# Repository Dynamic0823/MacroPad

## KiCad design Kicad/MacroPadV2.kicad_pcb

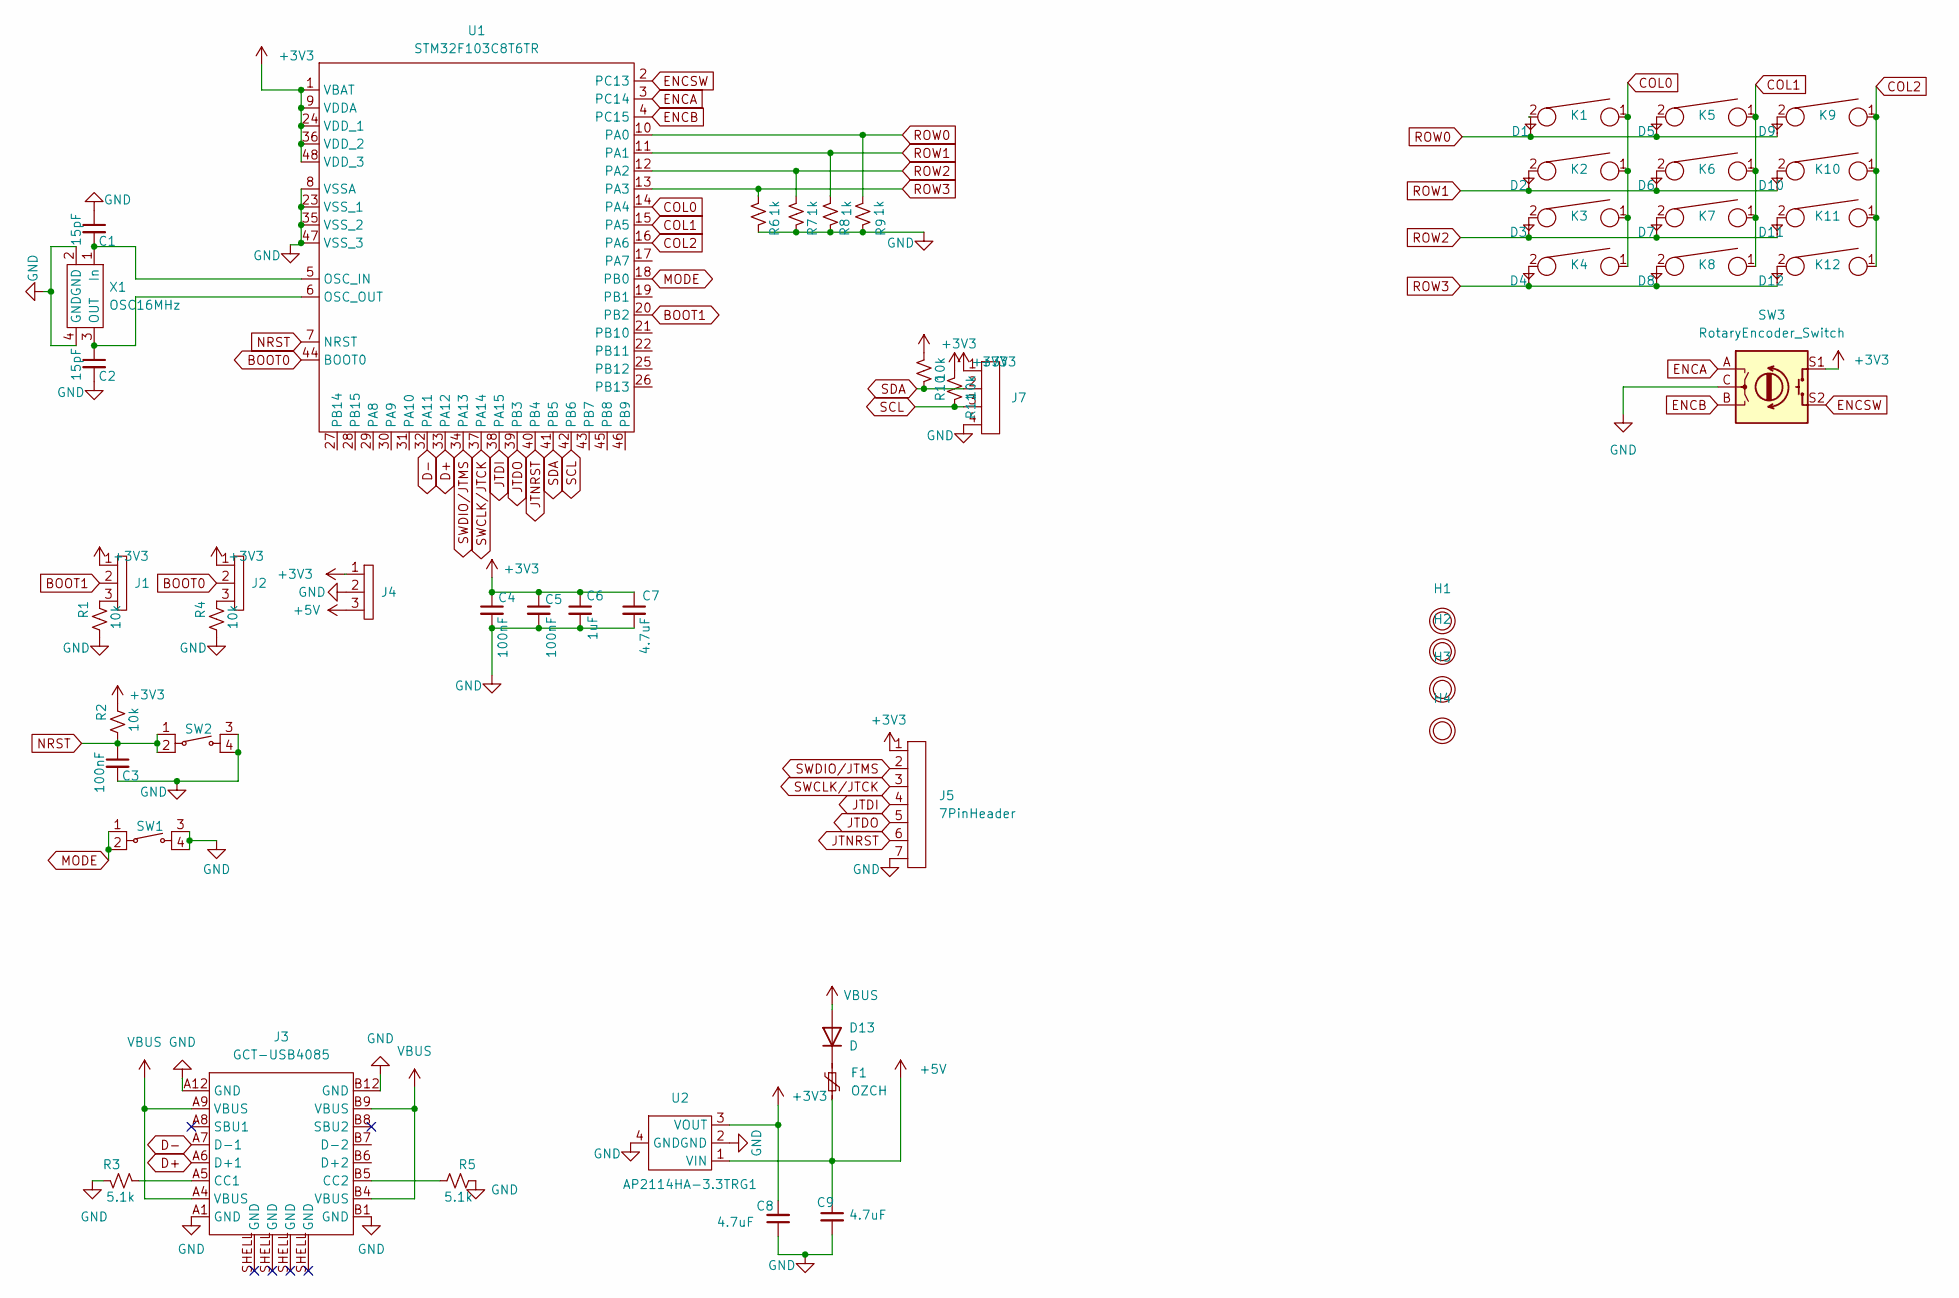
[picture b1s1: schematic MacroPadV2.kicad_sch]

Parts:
C1, C2: 15pF; C_0805_2012Metric_Pad1.18x1.45mm_HandSolder; DigikeyPN 311-1101-2-ND
C3, C4, C5: 100nF; C_0805_2012Metric_Pad1.18x1.45mm_HandSolder; DigikeyPN 3372-MT05B104M500BDTR-ND
C6: 1uF; C_0805_2012Metric_Pad1.18x1.45mm_HandSolder; DigikeyPN 1276-1003-2-ND
C7, C8, C9: 4.7uF; C_0805_2012Metric_Pad1.18x1.45mm_HandSolder; DigikeyPN 1276-1244-2-ND
D1, D2, D3, D4, D5, D6, D7, D8, D9, D10, D11, D12: TS4148 RBG; D_0805_2012Metric_Pad1.15x1.40mm_HandSolder; DigikeyPN 1801-TS4148RBGTR-ND
D13: D; D_0805_2012Metric_Pad1.15x1.40mm_HandSolder; DigikeyPN 1801-TS4148RBGTR-ND
F1: OZCH; OZCHFusr; DigikeyPN 507-1792-2-ND
H1, H2, H3, H4: M3Hole
J1, J2, J4: 3PinJump; PinHeader_1x03_P2.54mm_Vertical
J3: GCT-USB4085; USB4085-GF-A; DigikeyPN 2073-USB4085-GF-ATR-ND
J5: 7PinHeader; PinHeader_1x07_P2.54mm_Vertical
J7: 4PinJump; PinHeader_1x04_P2.54mm_Vertical
K1, K2, K3, K4, K5, K6, K7, K8, K9, K10, K11, K12: KSW; CherryMx; DigikeyPN CH197-ND
R1, R2, R4, R10, R11: 10k; R_0805_2012Metric_Pad1.20x1.40mm_HandSolder; DigikeyPN RMCF0805JT10K0TR-ND
R3, R5: 5.1k; R_0805_2012Metric_Pad1.20x1.40mm_HandSolder; DigikeyPN RMCF0805JT5K10TR-ND
R6, R7, R8, R9: 1k; R_0805_2012Metric_Pad1.20x1.40mm_HandSolder; DigikeyPN RMCF0805FT1K00
SW1, SW2: SWITCH_TACTILE_SPST-NO_0.05A_12V; PTS645-G; DigikeyPN CKN9085TR-ND
SW3: RotaryEncoder_Switch; PEC11H-RotaryEncoderSwitch; DigikeyPN 118-PEC11H-4220F-S0024-ND
U1: STM32F103C8T6TR; LQFP48; DigikeyPN 497-17666-2-ND
U2: AP2114HA-3.3TRG1; SOT-223_DIO-L; DigikeyPN AP2114HA-3.3TRG1DITR-ND
X1: TSX-3225_16.0000MF18X-AC6; TSX-3226; DigikeyPN SER4372TR-ND

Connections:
+3V3: C4.1, C5.1, C6.1, C7.1, C8.2, J1.1, J2.1, J4.1, J5.1, J7.1, R2.1, R10.2, R11.2, SW3.S1, U1.1 (VBAT), U1.9 (VDDA), U1.24 (VDD_1), U1.36 (VDD_2), U1.48 (VDD_3), U2.3 (VOUT)
+5V: C9.1, F1.2, J4.3, U2.1 (VIN)
BOOT0: J2.2, U1.44 (BOOT0)
BOOT1: J1.2, U1.20 (PB2)
COL0: K1.1, K2.1, K3.1, K4.1, U1.14 (PA4)
COL1: K5.1, K6.1, K7.1, K8.1, U1.15 (PA5)
COL2: K9.1, K10.1, K11.1, K12.1, U1.16 (PA6)
D+: J3.A6 (D+1), U1.33 (PA12)
D-: J3.A7 (D-1), U1.32 (PA11)
ENCA: SW3.A, U1.3 (PC14)
ENCB: SW3.B, U1.4 (PC15)
ENCSW: SW3.S2, U1.2 (PC13)
GND: C1.1, C2.2, C3.2, C4.2, C5.2, C6.2, C7.2, C8.1, C9.2, J3.A1 (GND), J3.A12 (GND), J3.B1 (GND), J3.B12 (GND), J4.2, J5.7, J7.4, R1.2, R3.1, R4.2, R5.1, R6.1, R7.1, R8.1, R9.1, SW1.3, SW1.4, SW2.3, SW2.4, SW3.C, U1.8 (VSSA), U1.23 (VSS_1), U1.35 (VSS_2), U1.47 (VSS_3), U2.2 (GND), U2.4 (GND), X1.2 (GND), X1.4 (GND)
JTDI: J5.4, U1.38 (PA15)
JTDO: J5.5, U1.39 (PB3)
JTNRST: J5.6, U1.40 (PB4)
MODE: SW1.1, SW1.2, U1.18 (PB0)
NRST: C3.1, R2.2, SW2.1, SW2.2, U1.7 (NRST)
unnamed: C1.2, U1.5 (OSC_IN), X1.1 (In)
unnamed: C2.1, U1.6 (OSC_OUT), X1.3 (OUT)
unnamed: D1.1, K1.2
unnamed: D2.1, K2.2
unnamed: D3.1, K3.2
unnamed: D4.1, K4.2
unnamed: D5.1, K5.2
unnamed: D6.1, K6.2
unnamed: D7.1, K7.2
unnamed: D8.1, K8.2
unnamed: D9.1, K9.2
unnamed: D10.1, K10.2
unnamed: D11.1, K11.2
unnamed: D12.1, K12.2
unnamed: D13.1 (K), F1.1
unnamed: J1.3, R1.1
unnamed: J2.3, R4.1
unnamed: J3.A5 (CC1), R3.2
unnamed: J3.B5 (CC2), R5.2
ROW0: D1.2, D5.2, D9.2, R9.2, U1.10 (PA0)
ROW1: D2.2, D6.2, D10.2, R8.2, U1.11 (PA1)
ROW2: D3.2, D7.2, D11.2, R7.2, U1.12 (PA2)
ROW3: D4.2, D8.2, D12.2, R6.2, U1.13 (PA3)
SCL: J7.3, R11.1, U1.42 (PB6)
SDA: J7.2, R10.1, U1.41 (PB5)
SWCLK/JTCK: J5.3, U1.37 (PA14)
SWDIO/JTMS: J5.2, U1.34 (PA13)
VBUS: D13.2 (A), J3.A4 (VBUS), J3.A9 (VBUS), J3.B4 (VBUS), J3.B9 (VBUS)

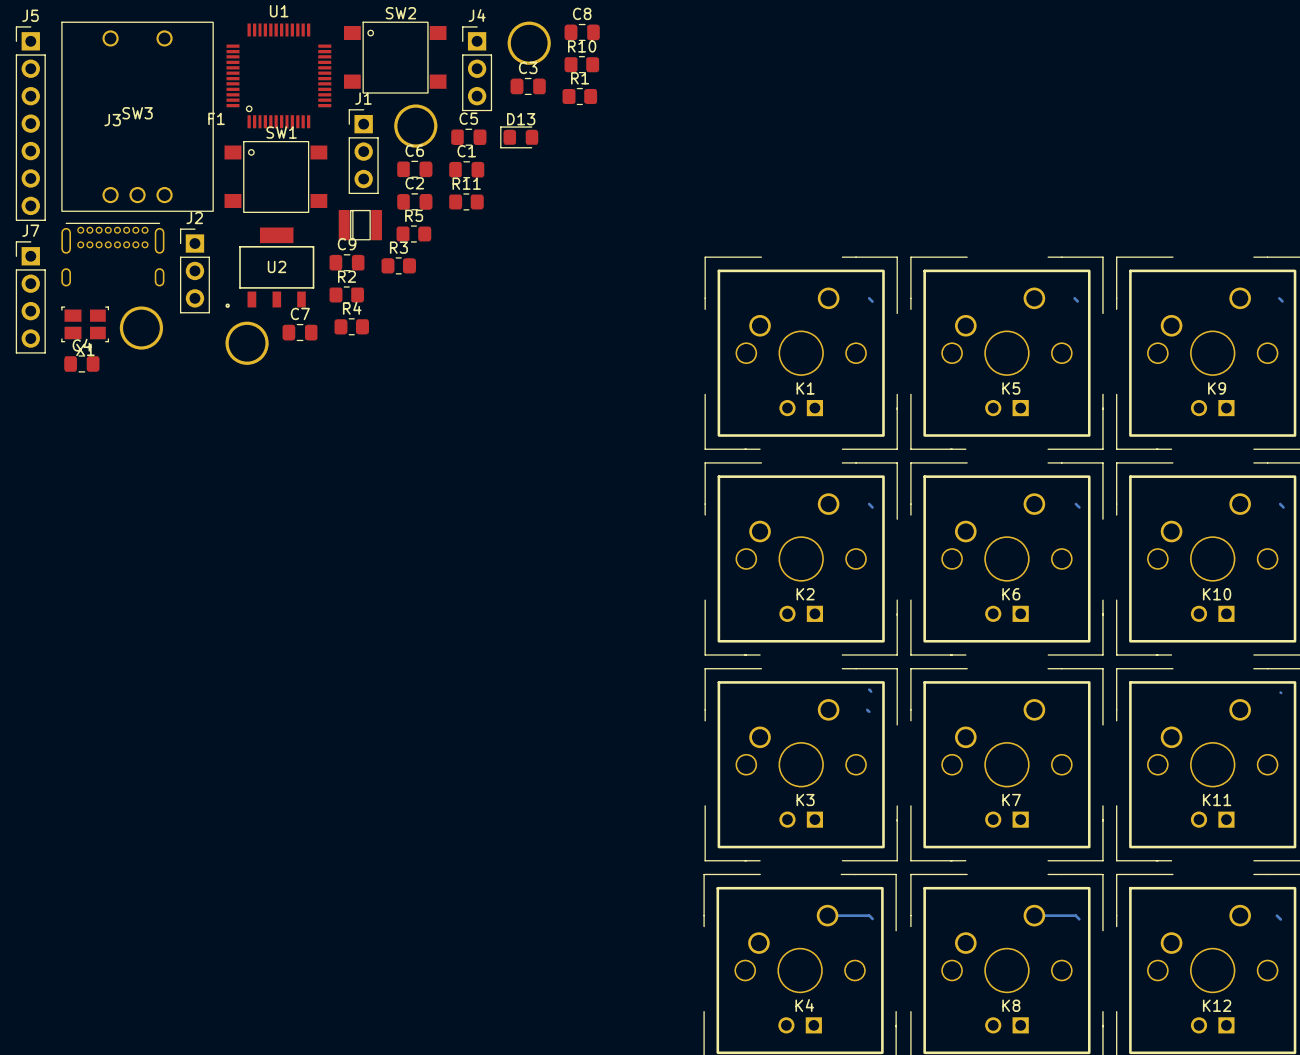
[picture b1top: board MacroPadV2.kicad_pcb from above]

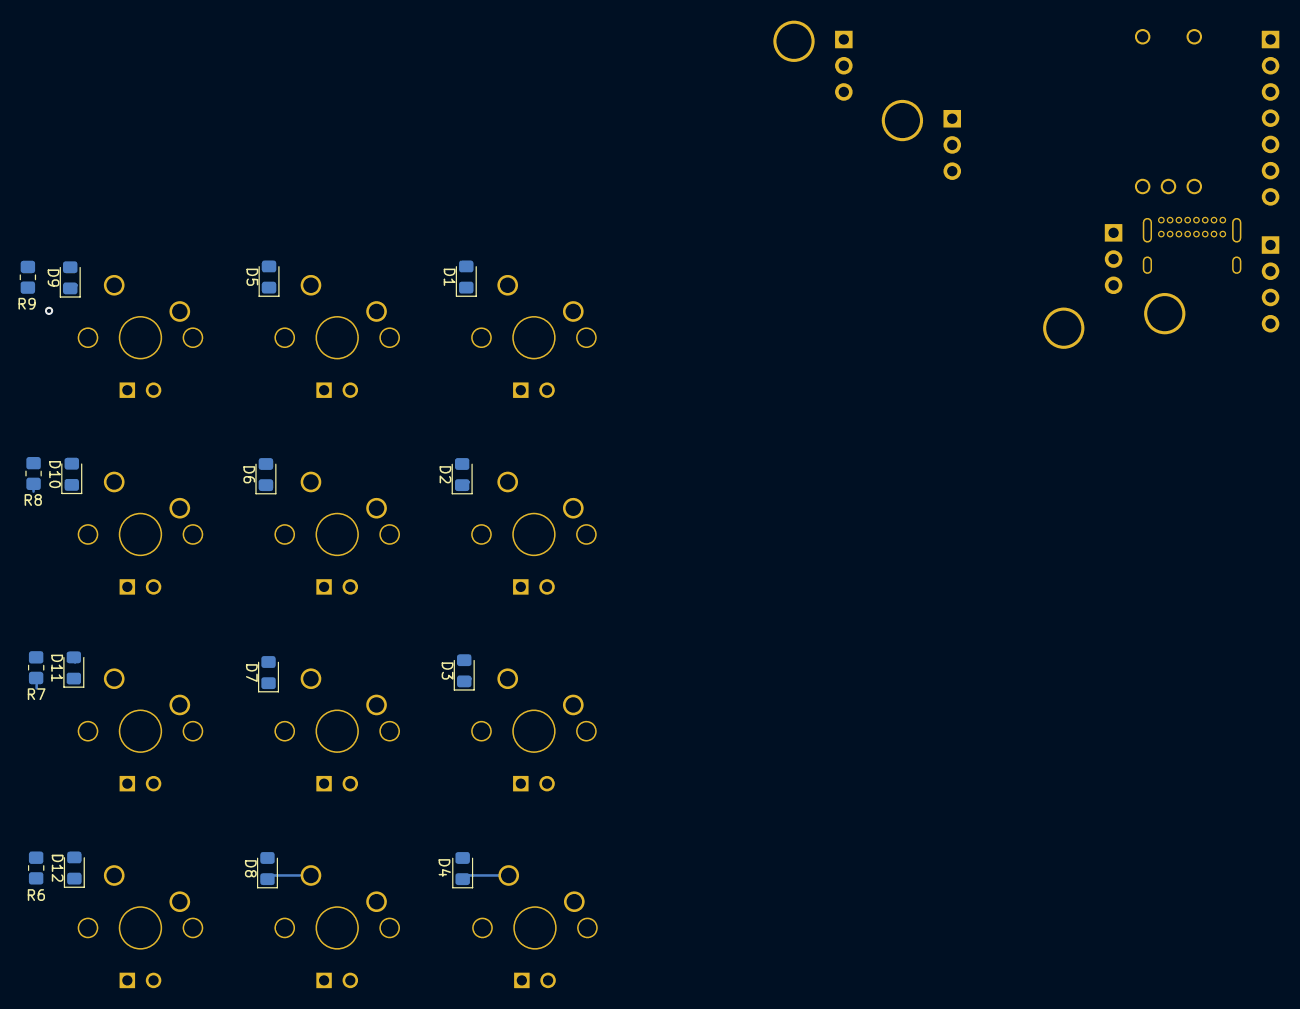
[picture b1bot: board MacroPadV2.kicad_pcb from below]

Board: 4 copper layers, 62 parts (16 on the bottom side), 46 nets.

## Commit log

2023-12-18 First Commit With Kicad Schem and Fps
2023-12-28 Added Arduino Project
2023-12-28 Started V2 -More space between keys(keycaps didnt fit) -Pull Down Resistors for Columns and Rotary Switch(ATMega32U4 is internal pull up) -Slightly larger board and edge holes
2023-12-28 Small changes
2023-12-28 Now we read the gpio port register for columns instead of doing 4 digitalReads. -Soldered Pull Down Resistors to Pull down lines -enc butt needs pull down -change target row/col each successful press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
2023-12-28 Edit: IM AN IDIOT -ROWS ARE THE INPUTS, COLS ARE THE OUTPUTS -Set Cols Low to read a set, then all high after -Removed Pull down resistors on cols
2023-12-29 Temp Branch for storing work that will be merged to v2
2023-12-29 V2 Schem and Routing Complete for drop in micro pro, making new branch for STM32F103
2023-12-29 New Branch for non-drop in cpu setup
2023-12-30 New LAyout an Routing done
2024-01-16 Fully Finished MacroPad V2 Schematic and Layout with stm32. Ordered and waiting for board to come in. -If there are no issues running the board, this should be the last commit for Kicad files. All pr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
2024-02-11 Removed some backups and push for swap to desktop
